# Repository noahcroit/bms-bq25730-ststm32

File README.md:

# bms-ti-bq25730-ststm32
BMS board development using BQ25730 chip from Texas Instrument. Testing firmware for host is based on STM32 MCU, using PlatformIO-ststm32 framework.

The project consists of
- `board`\
    KiCAD PCB layout for BMS board and schematic.

- `stm32`\
    BQ25730 C library based on arduino-stst32 (`stm32/lib/bq25730-ststm32`) + STM32F3disco example for BQ25730's host using PlatformIO framework.

### More to do
Add more supported functions for BQ25730 library
- Set charging and discharging current for the battery.
- Current limit and Voltage limit
- Be able to set the charging characteris to the chip based on battery type
- etc.

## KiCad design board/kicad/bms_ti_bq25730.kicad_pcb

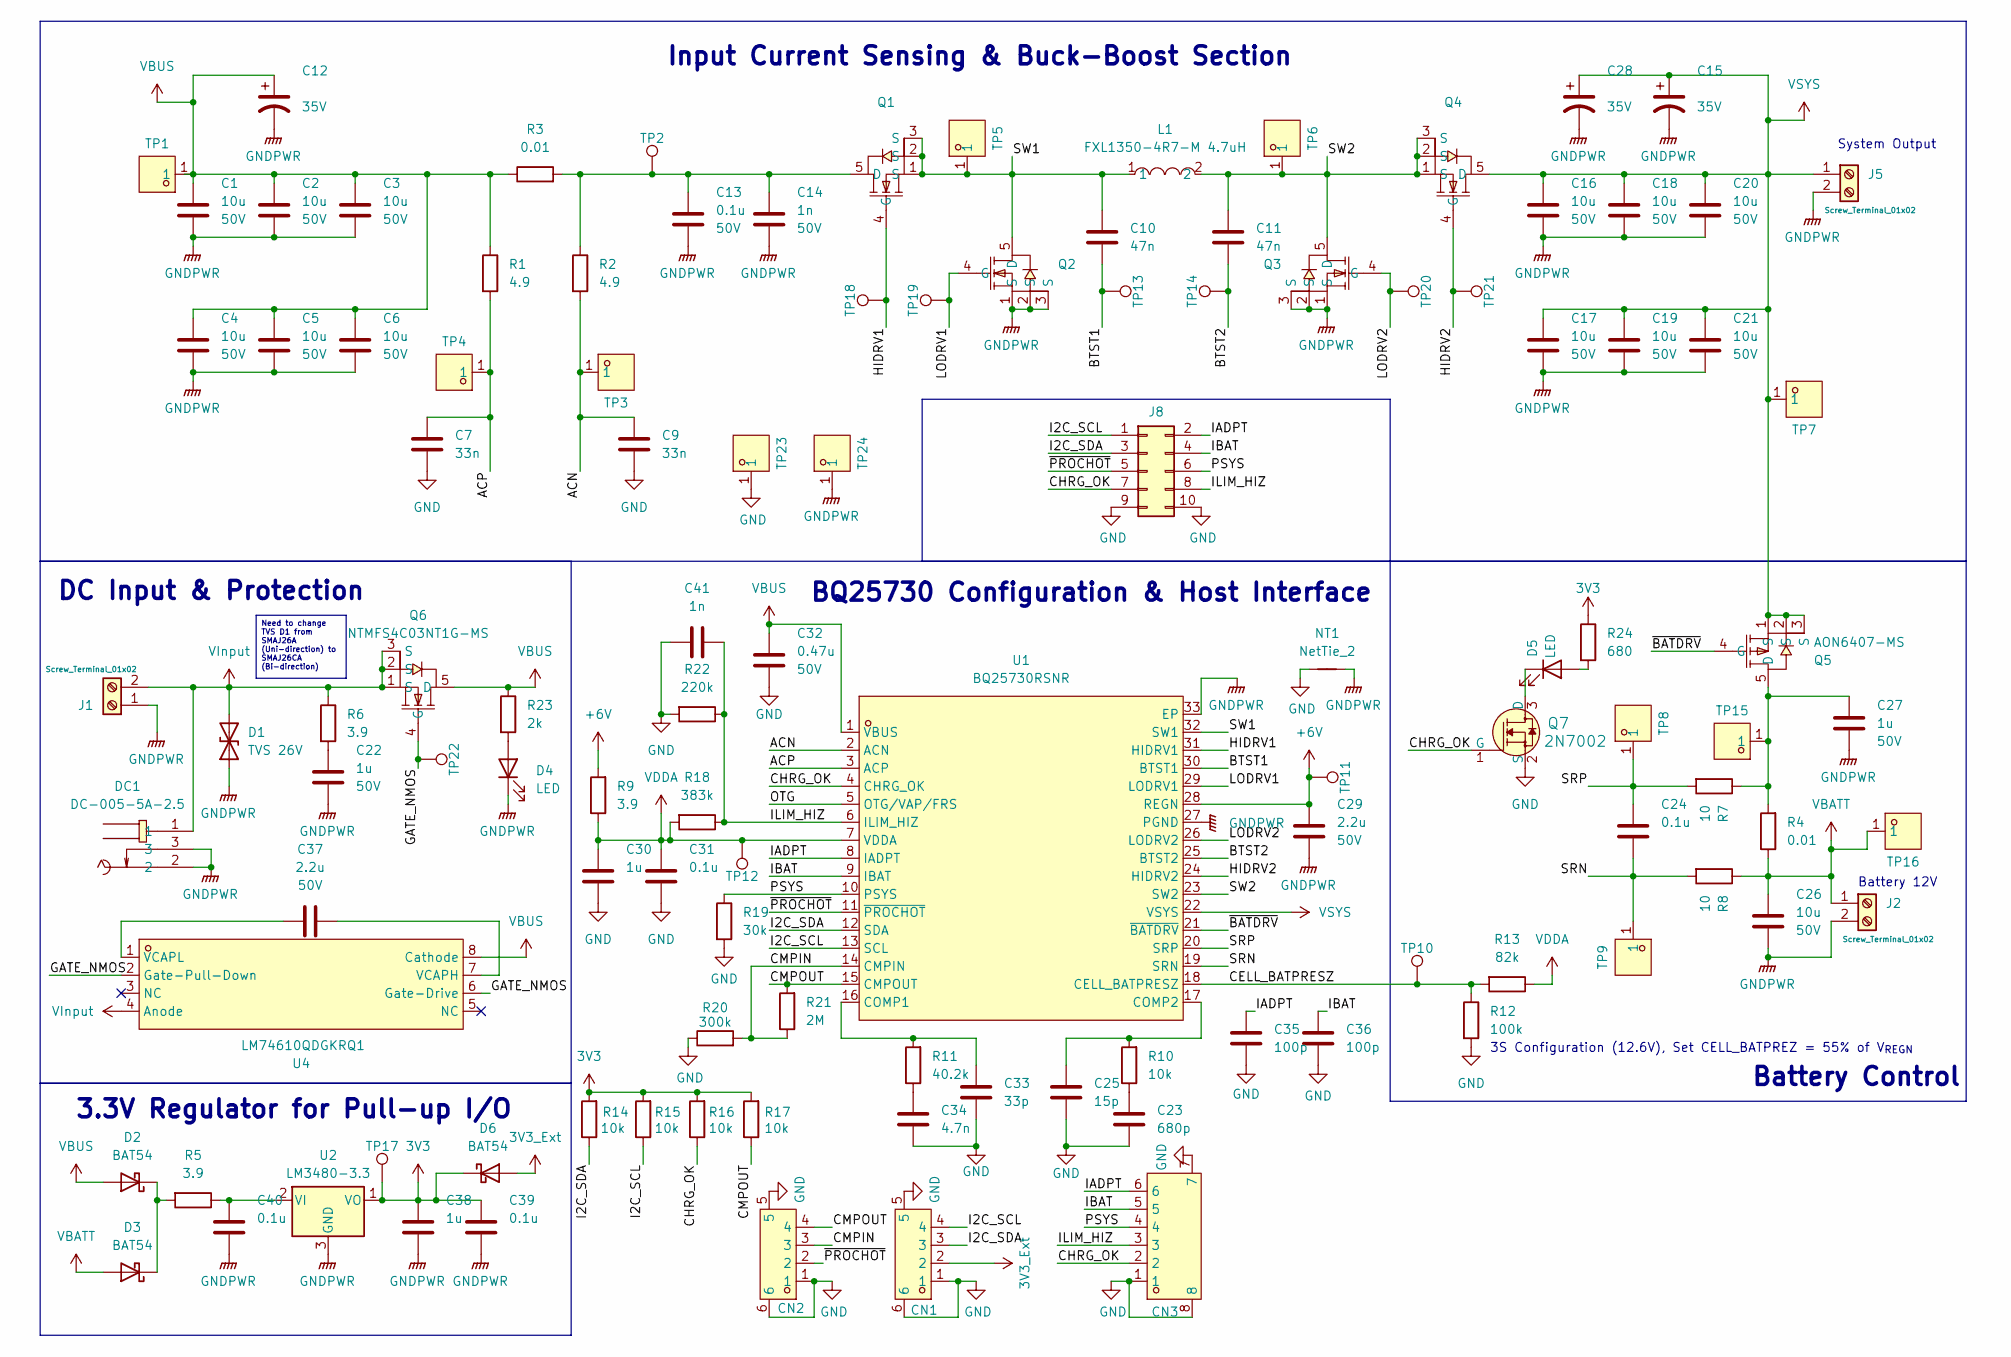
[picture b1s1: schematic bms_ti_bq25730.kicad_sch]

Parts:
C1, C2, C3, C4, C5, C6, C16, C17, C18, C19, C20, C21, C26: 10u; C_1206_3216Metric; Voltage 50V; Tolerance 100%; LCSC Part C920965
C7, C9: 33n; C_0603_1608Metric; Voltage 50V; Tolerance 100%; LCSC Part C165825
C10, C11: 47n; C_0603_1608Metric; Voltage 50V; Tolerance 100%; LCSC Part C342975
C12, C15, C28: C_Polarized; CP_EIA-7343-31_Kemet-D; Voltage 35V; Tolerance 100%; LCSC Part C696815
C13, C24, C31, C39, C40: 0.1u; C_0805_2012Metric; Voltage 50V; Tolerance 100%; LCSC Part C779984
C14, C41: 1n; C_0805_2012Metric; Voltage 50V; Tolerance 100%; LCSC Part C1791
C22, C27, C30, C38: 1u; C_1206_3216Metric; Voltage 50V; Tolerance 100%; LCSC Part C77099
C23: 680p; C_0603_1608Metric; Voltage 50V; Tolerance 100%; LCSC Part C3000825
C25: 15p; C_0603_1608Metric; Voltage 50V; Tolerance 100%; LCSC Part C302055
C29, C37: 2.2u; C_1206_3216Metric; Voltage 50V; Tolerance 100%; LCSC Part C282852
C32: 0.47u; C_1206_3216Metric; Voltage 50V; Tolerance 100%; LCSC Part C471384
C33: 33p; C_0603_1608Metric; Voltage 50V; Tolerance 100%; LCSC Part C597158
C34: 4.7n; C_0603_1608Metric; Voltage 50V; Tolerance 100%; LCSC Part C22376401
C35, C36: 100p; C_0603_1608Metric; Voltage 50V; Tolerance 100%; LCSC Part C343033
CN1, CN2: WAFER-200W-4A; CONN-SMD_4P-P2.00_HANBO_WAFER-200W-4A; LCSC Part C2874529
CN3: WAFER-200W-6A; CONN-SMD_6P-P2.00_XUNPU_WAFER-200W-6A; LCSC Part C2874531
D1: TVS 26V; D_SMA; LCSC Part C383698
D2, D3, D6: BAT54; D_SOD-323_HandSoldering; LCSC Part C5369354
D4: LED; LED_0805_2012Metric; LCSC Part C397047
D5: LED; LED_0805_2012Metric; LCSC Part C497949
DC1: DC-005-5A-2.5; DC-IN-TH_DC-005-5A-2.5; LCSC Part C381115
J1, J2, J5: Screw_Terminal_01x02; TerminalBlock_bornier-2_P5.08mm; LCSC Part C8465
J8: Conn_02x05_Odd_Even; PinHeader_2x05_P2.54mm_Vertical; LCSC Part C7501276
L1: FXL1350-4R7-M 4.7uH; IND-SMD_L12.6-W13.5; LCSC Part C526015
NT1: NetTie_2; NetTie-2_SMD_Pad0.5mm
Q1, Q2, Q3, Q4: AON6362-MS; TDSON-8_L5.9-W5.2-P1.27-BL; LCSC Part C17702960
Q5: AON6407-MS; TDSON-8_L5.9-W5.2-P1.27-BL; LCSC Part C17702953
Q6: NTMFS4C03NT1G-MS; TDSON-8_L5.9-W5.2-P1.27-BL; LCSC Part C17702949
Q7: 2N7002; SOT-23-3; MPN 2N7002; Digi-Key_PN 2N7002NCT-ND
R1, R2: 4.9; R_0603_1608Metric; LCSC Part C861449
R3, R4: 0.01; R_2512_6332Metric; LCSC Part C127692
R5, R6, R9: 3.9; R_1206_3216Metric; LCSC Part C17885
R7, R8: 10; R_0603_1608Metric; LCSC Part C22859
R10, R14, R15, R16, R17: 10k; R_0603_1608Metric; LCSC Part C469659
R11: 40.2k; R_0603_1608Metric; LCSC Part C491131
R12: 100k; R_0603_1608Metric; LCSC Part C25803
R13: 82k; R_0603_1608Metric; LCSC Part C351626
R18: 383k; R_0603_1608Metric; LCSC Part C5240674
R19: 30k; R_0603_1608Metric; LCSC Part C190612
R20: 300k; R_0603_1608Metric; LCSC Part C7468400
R21: 2M; R_0603_1608Metric; LCSC Part C2770823
R22: 220k; R_0603_1608Metric; LCSC C861231
R23: 2k; R_0603_1608Metric; LCSC Part C269690
R24: 680; R_0805_2012Metric; LCSC Part C543547
TP1, TP3, TP4, TP5, TP6, TP7, TP8, TP9, TP15, TP16, TP23, TP24: RH-5006; TH_BD3.2-D2.0; LCSC Part C5199811
TP2, TP10, TP11, TP12, TP13, TP14, TP17, TP18, TP19, TP20, TP21, TP22: 1.25mm; TestPoint-1.25mm
U1: BQ25730RSNR; QFN-32_L4.0-W4.0-P0.40-TL-EP2.8; LCSC Part C5219071
U2: LM3480-3.3; SOT-23; LCSC Part C5380665
U4: LM74610QDGKRQ1; VSSOP-8_L3.0-W3.0-P0.65-LS5.0-BL; LCSC Part C2649431

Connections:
3V3: C38.2, C39.2, D6.1 (K), R14.2, R15.2, R16.2, R17.2, R24.1, TP17.1, U2.1 (VO)
3V3_Ext: CN1.2, D6.2 (A)
+6V: C29.2, R9.2, TP11.1, U1.28 (REGN)
/ACN: C9.2, R2.2, TP3.1, U1.2 (ACN)
/ACP: C7.2, R1.2, TP4.1, U1.3 (ACP)
/BTST1: C10.1, TP13.1, U1.30 (BTST1)
/BTST2: C11.1, TP14.1, U1.25 (BTST2)
/CELL_BATPRESZ: R12.1, R13.2, TP10.1, U1.18 (CELL_BATPRESZ)
/CHRG_OK: CN3.2, J8.7, Q7.1 (G), R16.1, U1.4 (CHRG_OK)
/CMPIN: CN2.3, R20.2, R21.1, U1.14 (CMPIN)
/CMPOUT: CN2.4, R17.1, R21.2, U1.15 (CMPOUT)
/GATE_NMOS: Q6.4 (G), TP22.1, U4.2 (Gate-Pull-Down), U4.6 (Gate-Drive)
/HIDRV1: Q1.4 (G), TP18.1, U1.31 (HIDRV1)
/HIDRV2: Q4.4 (G), TP21.1, U1.24 (HIDRV2)
/I2C_SCL: CN1.4, J8.1, R15.1, U1.13 (SCL)
/I2C_SDA: CN1.3, J8.3, R14.1, U1.12 (SDA)
/IADPT: C35.1, CN3.6, J8.2, U1.8 (IADPT)
/IBAT: C36.1, CN3.5, J8.4, U1.9 (IBAT)
/ILIM_HIZ: C41.1, CN3.3, J8.8, R18.1, R22.1, U1.6 (ILIM_HIZ)
/LODRV1: Q2.4 (G), TP19.1, U1.29 (LODRV1)
/LODRV2: Q3.4 (G), TP20.1, U1.26 (LODRV2)
/OTG: U1.5 (OTG/VAP/FRS)
/PSYS: CN3.4, J8.6, R19.1, U1.10 (PSYS)
/SRN: C24.1, R8.2, TP9.1, U1.19 (SRN)
/SRP: C24.2, R7.2, TP8.1, U1.20 (SRP)
/SW1: C10.2, L1.1, Q1.1 (S), Q1.2 (S), Q1.3 (S), Q2.5 (D), TP5.1, U1.32 (SW1)
/SW2: C11.2, L1.2, Q3.5 (D), Q4.1 (S), Q4.2 (S), Q4.3 (S), TP6.1, U1.23 (SW2)
/~BATDRV: Q5.4 (G), U1.21 (~BATDRV)
/~PROCHOT: CN2.2, J8.5, U1.11 (~PROCHOT)
GND: C7.1, C9.1, C23.1, C25.2, C30.1, C31.1, C32.1, C33.2, C34.1, C35.2, C36.2, C41.2, CN1.1, CN1.5, CN1.6, CN2.1, CN2.5, CN2.6, CN3.1, CN3.7, CN3.8, J8.9, J8.10, NT1.1, Q7.2 (S), R12.2, R19.2, R20.1, R22.2, TP23.1
GNDPWR: C1.1, C2.1, C3.1, C4.1, C5.1, C6.1, C12.2, C13.1, C14.1, C15.2, C16.1, C17.1, C18.1, C19.1, C20.1, C21.1, C22.1, C26.1, C27.2, C28.2, C29.1, C38.1, C39.1, C40.1, D1.1 (A1), D4.1 (K), DC1.2, DC1.3, J1.1, J2.2, J5.2, NT1.2, Q2.1 (S), Q2.2 (S), Q2.3 (S), Q3.1 (S), Q3.2 (S), Q3.3 (S), TP24.1, U1.27 (PGND), U1.33 (EP), U2.3 (GND)
unnamed: C22.2, R6.2
unnamed: C23.2, R10.1
unnamed: C34.2, R11.1
unnamed: D2.1 (K), D3.1 (K), R5.2
unnamed: D4.2 (A), R23.2
unnamed: D5.2 (A), R24.2
unnamed: D5.1 (K), Q7.3 (D)
unnamed: C13.2, C14.2, Q1.5 (D), R2.1, R3.2, TP2.1
unnamed: C27.1, Q5.5 (D), R4.2, R7.1, TP15.1
unnamed: C33.1, R11.2, U1.16 (COMP1)
unnamed: C25.1, R10.2, U1.17 (COMP2)
unnamed: C40.2, R5.1, U2.2 (VI)
unnamed: C37.1, U4.7 (VCAPH)
unnamed: C37.2, U4.1 (VCAPL)
VBATT: C26.2, D3.2 (A), J2.1, R4.1, R8.1, TP16.1
VBUS: C1.2, C2.2, C3.2, C4.2, C5.2, C6.2, C12.1, C32.2, D2.2 (A), Q6.5 (D), R1.1, R3.1, R23.1, TP1.1, U1.1 (VBUS), U4.8 (Cathode)
VDDA: C30.2, C31.2, R9.1, R13.1, R18.2, TP12.1, U1.7 (VDDA)
VInput: D1.2 (A2), DC1.1, J1.2, Q6.1 (S), Q6.2 (S), Q6.3 (S), R6.1, U4.4 (Anode)
VSYS: C15.1, C16.2, C17.2, C18.2, C19.2, C20.2, C21.2, C28.1, J5.1, Q4.5 (D), Q5.1 (S), Q5.2 (S), Q5.3 (S), TP7.1, U1.22 (VSYS)

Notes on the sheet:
Need to change TVS D1 from SMAJ26A (Uni-direction) to SMAJ26CA (Bi-direction)
DC Input & Protection
Battery Control
Input Current Sensing & Buck-Boost Section
System Output
3S Configuration (12.6V), Set CELL_BATPREZ = 55% of V_{REGN}
Battery 12V
BQ25730 Configuration & Host Interface
3.3V Regulator for Pull-up I/O

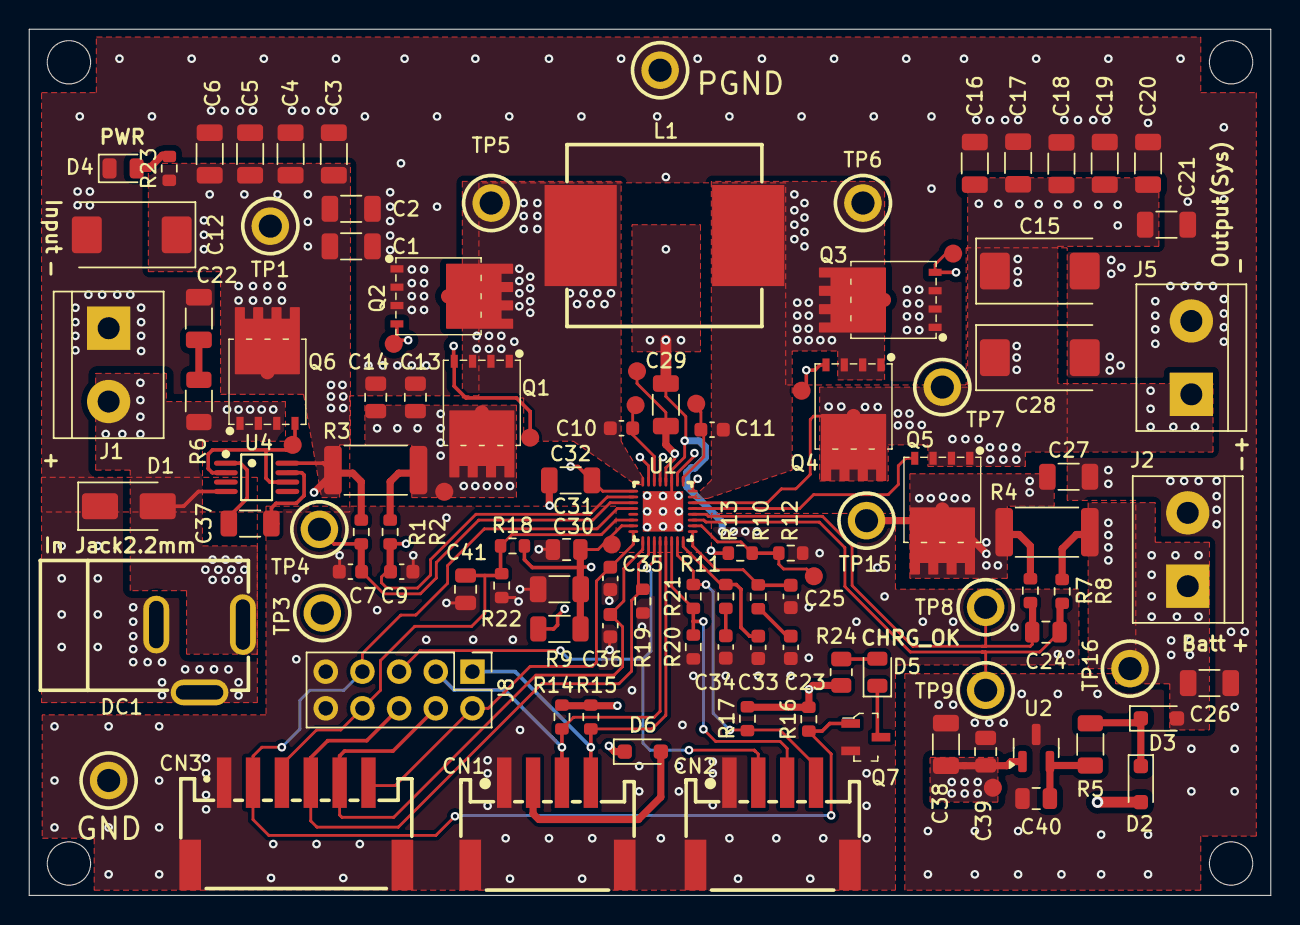
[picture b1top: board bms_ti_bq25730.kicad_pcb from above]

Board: 4 copper layers, 86.0 x 60.0 mm, 114 parts (1 on the bottom side), 49 nets.

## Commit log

2024-12-11 add kicad files for bms board
2024-12-11 create image folder, store images of BMS board
2024-12-11 add stm32 firmware for the host of BQ25730 chip in BMS board
2024-12-11 rm pio/build
2024-12-11 adjust image in readme
2024-12-12 lib/bq25730 : prepare the lib to be used in other framework (STM32Cube, Zephyr etc)
2024-12-12 create init function for bq25730
2024-12-13 lib/bq25730 : add set charge current function
2024-12-13 test firmware, update main
2024-12-13 lib/bq25730 : add set v charge and update
2024-12-13 update main, adding the charge current setting
